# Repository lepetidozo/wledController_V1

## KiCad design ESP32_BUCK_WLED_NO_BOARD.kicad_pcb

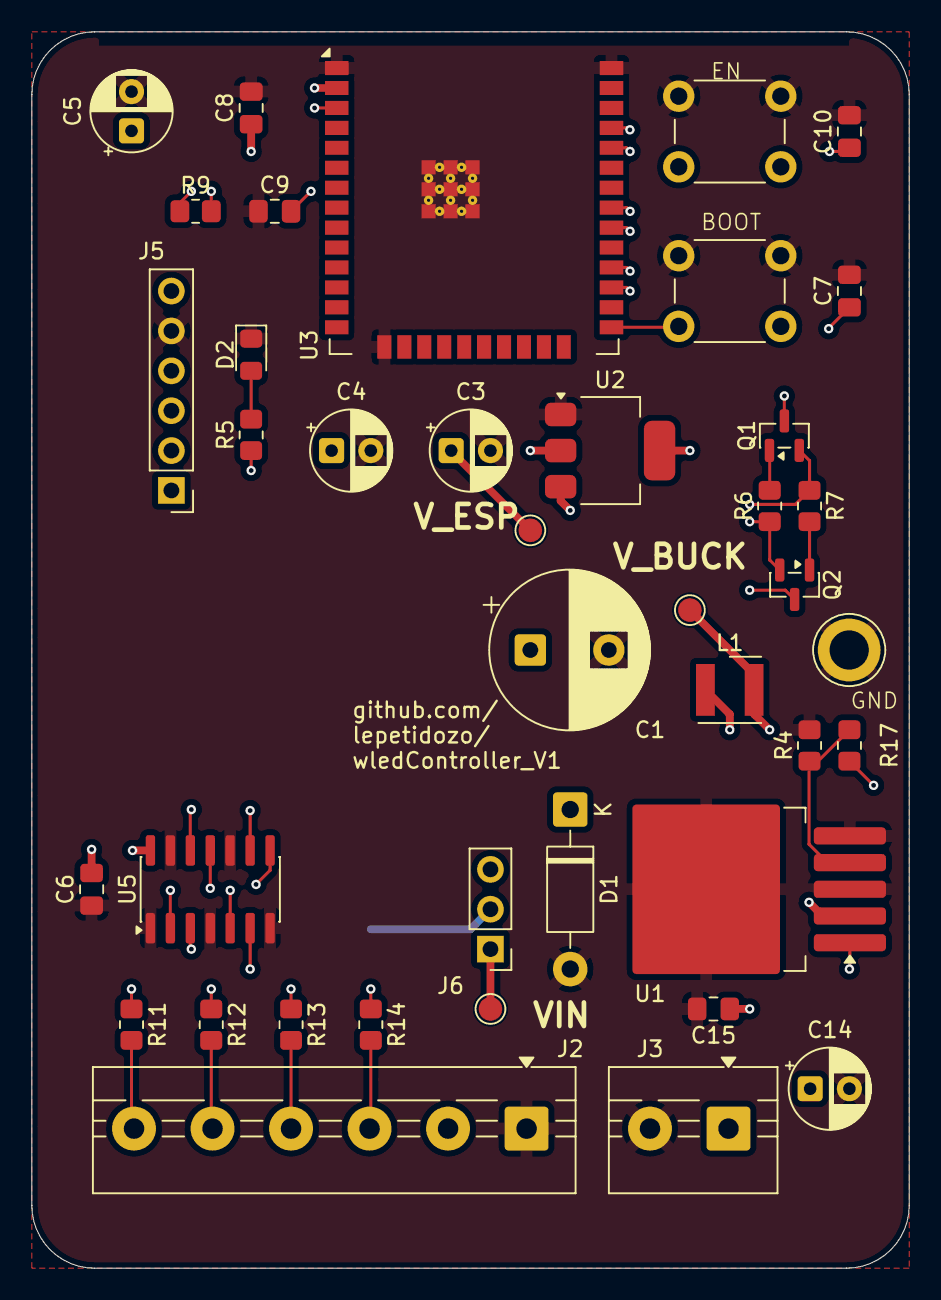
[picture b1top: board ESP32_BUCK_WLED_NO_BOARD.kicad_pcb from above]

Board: 4 copper layers, 55.9 x 78.7 mm, 40 parts (0 on the bottom side), 28 nets.

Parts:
C1: 470uF; CP_Radial_D10.0mm_P5.00mm
C3, C4, C5: 47uF; CP_Radial_D5.0mm_P2.50mm
C6, C7, C8, C9, C10: 0.1uF; C_0805_2012Metric_Pad1.18x1.45mm_HandSolder
C14: 100uF(50V); CP_Radial_D5.0mm_P2.50mm
C15: 0.1uF(50V); C_0805_2012Metric_Pad1.18x1.45mm_HandSolder
D1: 1N5822; D_DO-41_SOD81_P10.16mm_Horizontal
D2: RED LED; LED_0805_2012Metric_Pad1.15x1.40mm_HandSolder
J2: LEDSTRIPS_DATA_ALIMENTATIION; TerminalBlock_MaiXu_MX126-5.0-06P_1x06_P5.00mm
J3: BOARD_ALIMENTATION; TerminalBlock_MaiXu_MX126-5.0-02P_1x02_P5.00mm
J5: ESP_FLASH_PIN; PinHeader_1x06_P2.54mm_Vertical
J6: Conn_01x03; PinHeader_1x03_P2.54mm_Vertical
L1: 68uH; L_Wurth_WE-LQSH-4020
Q1, Q2: SS8050; SOT-23
R4, R5: 1K; R_0805_2012Metric_Pad1.20x1.40mm_HandSolder
R6, R7, R9: 10K; R_0805_2012Metric_Pad1.20x1.40mm_HandSolder
R11, R12, R13, R14: 330R; R_0805_2012Metric_Pad1.20x1.40mm_HandSolder
R17: 3K; R_0805_2012Metric_Pad1.20x1.40mm_HandSolder
SW2, SW3: SW_Push; SW_PUSH_6mm
TP1, TP3, TP5: TestPoint; TestPoint_Pad_D1.5mm
TP2: TestPoint; TestPoint_Loop_D3.80mm_Drill2.5mm
U1: LM2596T-ADJ; TO-263-5_TabPin3
U2: AMS1117-3.3; SOT-223-3_TabPin2
U3: ESP32-WROOM-32E
U5: 74AHCT125; SOIC-14_3.9x8.7mm_P1.27mm

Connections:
/5V_BUCK: C1.1, J6.3, L1.2, R17.1, TP3.1 (1_1)
/5V_ESP: C4.1, C6.2, J6.2, R5.1, U2.3 (VI), U5.14 (VCC)
/DTR: J5.1, Q2.2 (E), R6.2
/EN: C9.1, C10.1, Q1.3 (C), R9.1, SW3.2, U3.3 (EN)
/IO0: C7.1, Q2.3 (C), SW2.2, U3.25 (IO0)
/IO16: U3.27 (IO16), U5.2
/IO17: U3.28 (IO17), U5.5
/IO18: U3.30 (IO18), U5.9
/IO19: U3.31 (IO19), U5.12
/LED1: R14.1, U5.3
/LED2: R13.1, U5.6
/LED3: R12.1, U5.8
/LED4: R11.1, U5.11
/RTS: J5.2, Q1.2 (E), R7.2
/RXD: J5.4, U3.35 (TXD0/IO1)
/RXD0: J5.3, U3.34 (RXD0/IO3)
/VDD33: C3.1, C5.1, C8.1, J5.6, R9.2, TP5.1 (1_1), U2.2 (VO), U3.2 (VDD)
/V_ALIM: C14.1, C15.1, J2.2, J3.1, J6.1, TP1.1 (1_1), U1.1 (VIN)
GND: C1.2, C3.2, C4.2, C5.2, C6.1, C7.2, C8.2, C9.2, C10.2, C14.2, C15.2, D1.2 (A), D2.1 (K), J2.1, J3.2, J5.5, R4.2, SW2.1, SW3.1, TP2.1 (1_1), U1.3 (GND), U1.5 (~ON/OFF), U2.1 (GND), U3.1 (GND), U3.15 (GND), U3.38 (GND), U3.39 (GND), U5.1, U5.4, U5.7 (GND), U5.10, U5.13
unnamed: D1.1 (K), L1.1, U1.2 (OUT)
unnamed: D2.2 (A), R5.2
unnamed: J2.3, R14.2
unnamed: J2.4, R13.2
unnamed: J2.5, R12.2
unnamed: J2.6, R11.2
unnamed: Q1.1 (B), R6.1
unnamed: Q2.1 (B), R7.1
unnamed: R4.1, R17.2, U1.4 (FB)
